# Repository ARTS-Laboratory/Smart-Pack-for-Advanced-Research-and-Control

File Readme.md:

# Smart-Pack-for-Advanced-Research-and-Control (SPARC)
The SPARC Pack is an open-source, research-grade battery system designed to advance thermal and electro-thermal modeling techniques while integrating state-of-the-art sensing and Battery Management System (BMS) technologies. Its modular design supports both cylindrical and pouch cell configurations, enabling cutting-edge investigations into battery performance, health, and reliability under diverse operating conditions.

## Variations

### Camden
A pack designed around the Samsung 30Q as a 10S1P nominal 40 V pack. 

## Licensing and Citation

This work is licensed under a Creative Commons Attribution-ShareAlike 4.0 International License [cc-by-sa 4.0].

Cite this as: 

@Misc{ARTSLabSmartPackAdvanced,    
  author = {ARTS-Lab},  
  howpublished = {GitHub},  
  title  = {Smart-Pack-for-Advanced-Research-and-Control},    
  groups = {ARTS-Lab},    
  url    = {https://github.com/ARTS-Laboratory/Smart-Pack-for-Advanced-Research-and-Control},   
  note  = {Accessed: Month dd, yyyy},   
}

<p align="center">
QR code for repo.
</p>

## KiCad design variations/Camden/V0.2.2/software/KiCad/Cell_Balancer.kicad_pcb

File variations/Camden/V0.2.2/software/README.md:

# Software

## Todo
1. Save in the correct KiCAD version.

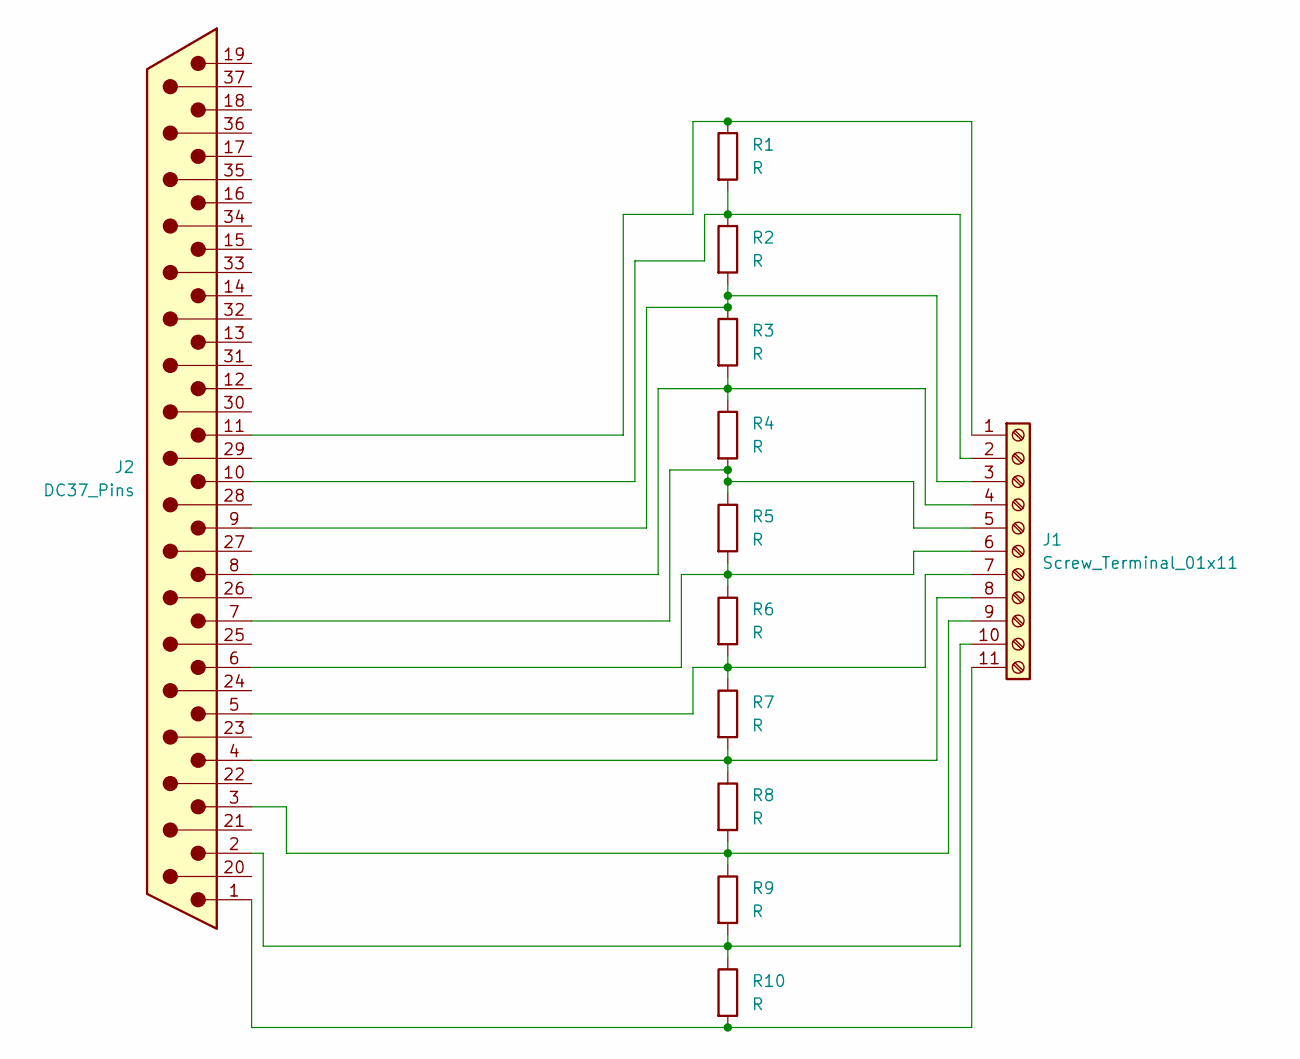
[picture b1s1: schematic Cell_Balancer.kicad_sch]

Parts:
J1: Screw_Terminal_01x11; TerminalBlock_Phoenix_MKDS-1,5-11_1x11_P5.00mm_Horizontal
J2: DC37_Pins; DSUB-37_Pins_Horizontal_P2.77x2.84mm_EdgePinOffset9.90mm_Ho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
R1, R2, R3, R4, R5, R6, R7, R8, R9, R10: R; R_1812_4532Metric

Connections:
unnamed: J1.1, J2.11, R1.1
unnamed: J1.2, J2.10, R1.2, R2.1
unnamed: J1.3, J2.9, R2.2, R3.1
unnamed: J1.4, J2.8, R3.2, R4.1
unnamed: J1.5, J2.7, R4.2, R5.1
unnamed: J1.6, J2.6, R5.2, R6.1
unnamed: J1.7, J2.5, R6.2, R7.1
unnamed: J1.8, J2.4, R7.2, R8.1
unnamed: J1.9, J2.3, R8.2, R9.1
unnamed: J1.10, J2.2, R9.2, R10.1
unnamed: J1.11, J2.1, R10.2

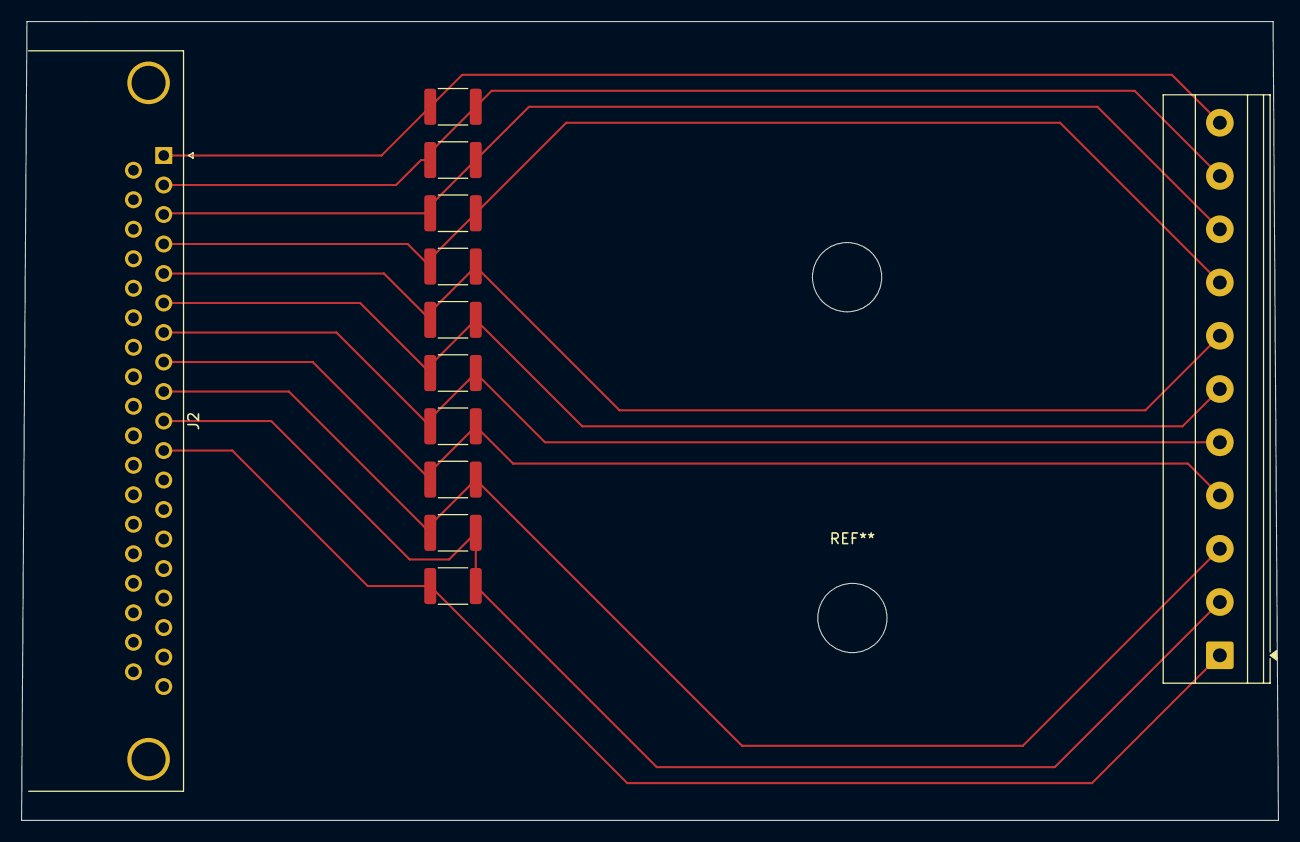
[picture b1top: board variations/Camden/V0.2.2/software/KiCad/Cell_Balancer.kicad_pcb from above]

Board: 2 copper layers, 118.0 x 75.0 mm, 12 parts (0 on the bottom side), 11 nets.

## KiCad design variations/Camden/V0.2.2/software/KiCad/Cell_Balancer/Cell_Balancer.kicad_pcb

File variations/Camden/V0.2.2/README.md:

# Camden V0.2.2
This version puts the pack onto a back board with a DIN Rail

This project uses KiCAD 9.0.5 https://downloads.kicad.org/kicad/windows/explore/stable/download/kicad-9.0.5-x86_64.exe and Inventor 2025 Q2

 <br> 
<p style="text-align: center;"> Desing vison image of the proposed SPARC system.</p>

</p>

 <br> 
<p style="text-align: center;"> The battery pack design.</p>

</p>

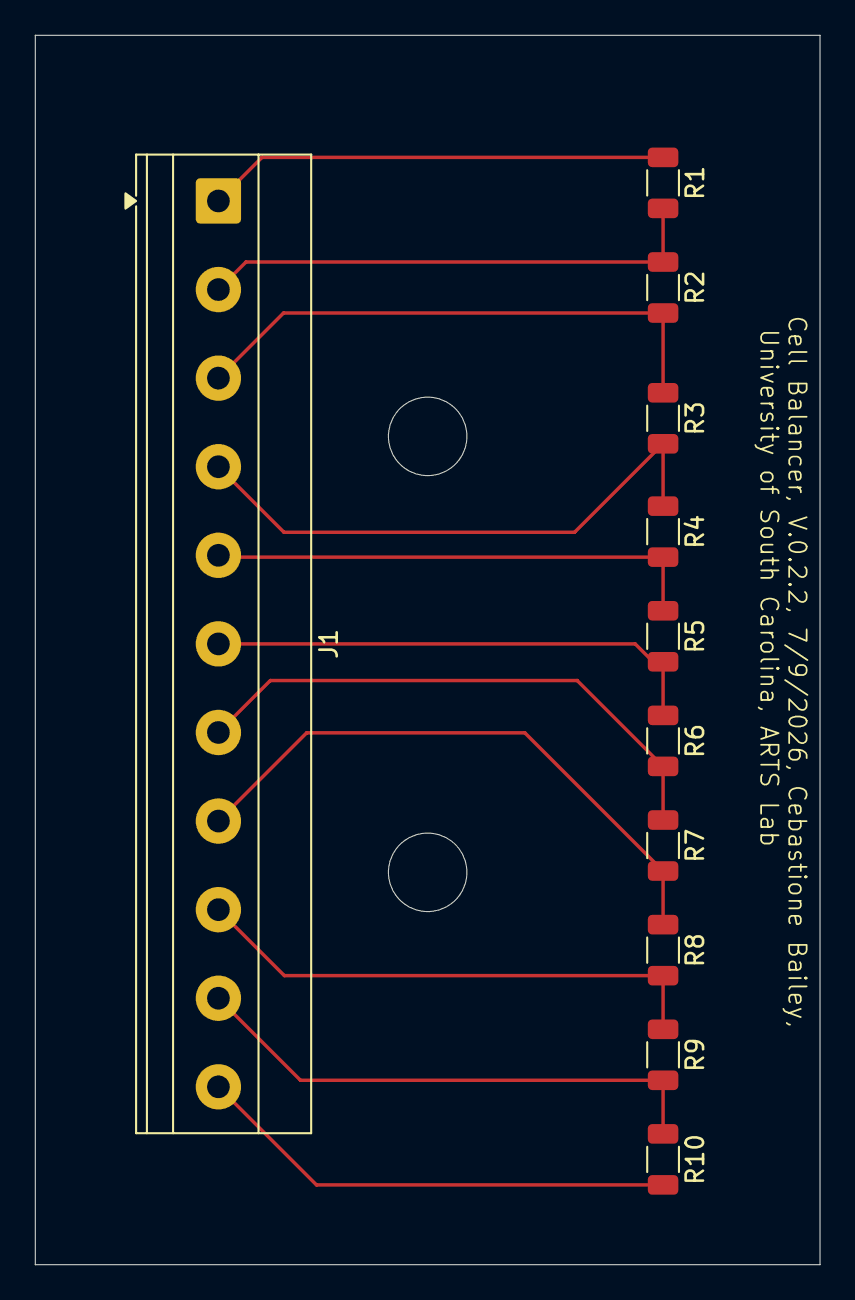
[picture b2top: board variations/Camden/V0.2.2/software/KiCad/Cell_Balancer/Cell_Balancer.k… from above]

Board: 2 copper layers, 45.0 x 70.5 mm, 11 parts (0 on the bottom side), 11 nets.

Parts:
J1: Screw_Terminal_01x11; TerminalBlock_Phoenix_MKDS-1,5-11-5.08_1x11_P5.08mm_Horizon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
R1, R2, R3, R4, R5, R6, R7, R8, R9, R10: R; R_1206_3216Metric

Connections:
unnamed: J1.1, R1.1
unnamed: J1.2, R1.2, R2.1
unnamed: J1.3, R2.2, R3.1
unnamed: J1.4, R3.2, R4.1
unnamed: J1.5, R4.2, R5.1
unnamed: J1.6, R5.2, R6.1
unnamed: J1.7, R6.2, R7.1
unnamed: J1.8, R7.2, R8.1
unnamed: J1.9, R8.2, R9.1
unnamed: J1.10, R9.2, R10.1
unnamed: J1.11, R10.2

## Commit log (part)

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2024-12-09 initial push
2025-02-14 Cad and slicer files
    These are the CAD and slicer files for the 3 variations of the battery pack. the .ipt files were made in inventor and the .stl are made with the bambu slicer
2025-02-26 Cad and Slicer Files
2025-02-28 CAD file
    Variation 2 involves having a male and female pillar in order to help facilitate good thermal contact
2025-03-03 IPT files
2025-03-03 CAD files
2025-03-04 ipt files
    The pillars now make contact on the make and female sections, instead of just being slots
2025-03-04 ipt file
    This 3d model is a tool to make sure the tolerance on the main part is good
2025-03-04 Slicer files
2025-03-04 Stress test
    This is the data gathered from a stress test performed on the 18650 pack
2025-03-05 added figure to Camden v0.2
2025-03-06 Figure Update
2025-03-06 added design document
2025-03-07 update design document
2025-03-07 added 20k price to total system
2025-03-07 update design documents
2025-03-07 update slide deck
2025-03-13 updated exploded view image
2025-03-18 updae
2025-06-10 Added pillars case for the 21700 cell
2025-08-08 Added project box CAD
2025-08-10 2nd CAD model added
2025-08-10 labeled CAD Models
2025-09-18 Camden BOM
2025-09-18 added tee to BOM
2025-09-19 added v0.2.1
2025-09-19 updated BOM
2025-09-25 Clean Up
    Deleted files that are dependent on non existing files, will replace them later. organized the cad models based on their cell type. deleted redundant files
2025-09-27 updated BOM with 3/8 pluming parts
2025-09-30 embossing
    Changed the embossing on the pack cad file. this will need to be updated every time the model is printed
2025-10-10 new print
2025-10-22 Update
    made slight alteration to pack model to account for tubes poking out of cooling plate
2025-10-27 Added a part to BOM
2026-01-05 Updated BOM
    added spring
2026-01-07 adjusted the snap in place component of the cell holder
2026-03-07 Made a second cooling plate. Simple rectangle made of aluminum
2026-03-07 changed design of the cellcase
2026-04-02 made improvements to cad model
2026-04-02 changed dimensions of the convection plate
2026-04-08 updated dessign
2026-04-15 added tolerances, and a way to check if tolerance is good
2026-04-17 added more materials to the BOM
2026-05-12 fixed dimensional issues in both original coooling plate and convection cooling plate
2026-05-21 New Case
    Added a new version with the newest case. this required a new folder because it is a major redesign
2026-06-03 added materials to BOM
2026-06-03 moved us back to 0.2.1
2026-06-20 added vision image
2026-06-24 added software items
    Added a simulation of the battery pack with our cell balancer as well as a pcb schematic
2026-06-29 Update BOM-SPARC-Camden-V0.2.1.xlsx
    added new sstraingauge vendor
